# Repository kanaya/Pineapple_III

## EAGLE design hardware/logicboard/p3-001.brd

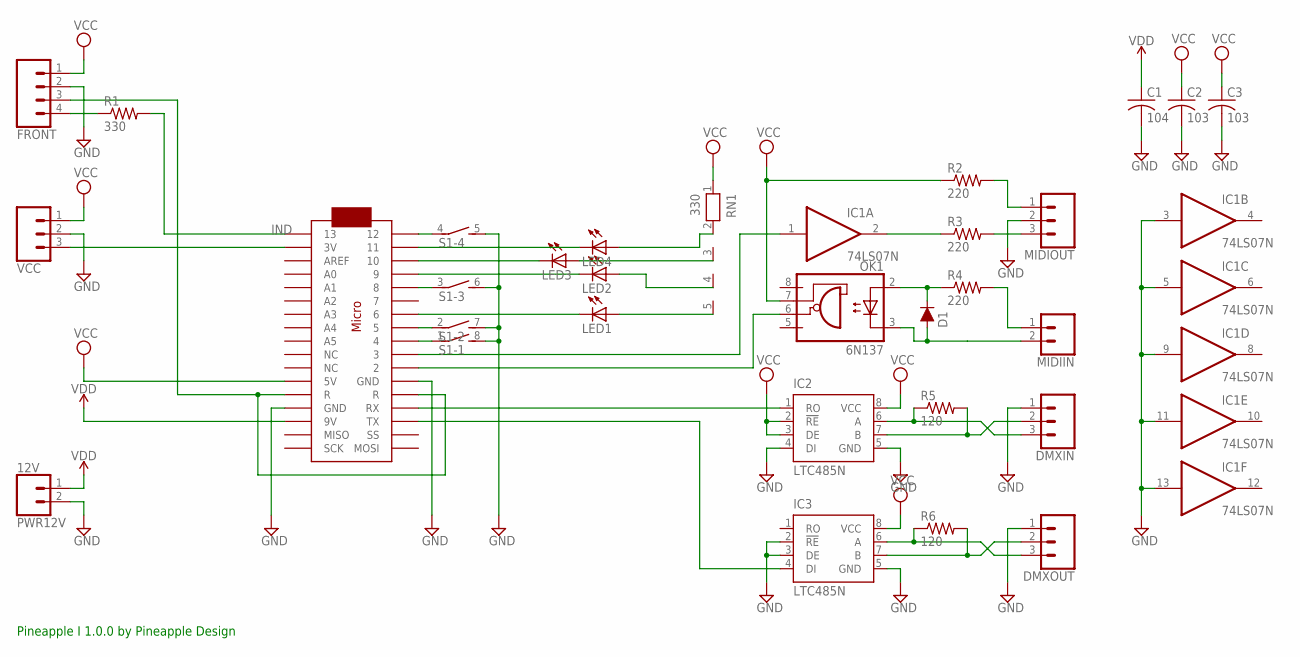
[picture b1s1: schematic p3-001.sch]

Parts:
C1: 104; C025-025X050
C2, C3: 103; C025-025X050
D1: DIODE-1N4148
DMXIN: CONN_03JST-PTH; JST-3-PTH
DMXOUT: CONN_03JST-PTH; JST-3-PTH
FRONT: CONN_04JST-PTH; JST-4-PTH
IC1: 74LS07N; DIL14
IC2, IC3: LTC485N; DIL08
LED1, LED2, LED3, LED4: LED3MM
MIDIIN: CONN_02JST-PTH-2; JST-2-PTH
MIDIOUT: CONN_03JST-PTH; JST-3-PTH
OK1: 6N137; DIL08
PWR12V: 12V; JST-2-PTH
R1: 330; 0204/5
R2, R3, R4: 220; 0204/5
R5, R6: 120; 0204/5
RN1: 330; RN-5
S1: DIP04S
U$1: ARDUINOMICRO
VCC: CONN_03JST-PTH; JST-3-PTH

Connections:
GND: C1.2, C2.2, C3.2, DMXIN.1, DMXOUT.1, FRONT.2, IC1.3 (I), IC1.5 (I), IC1.7 (GND), IC1.9 (I), IC1.11 (I), IC1.13 (I), IC2.4 (DI), IC2.5 (GND), IC3.2 (!RE), IC3.3 (DE), IC3.5 (GND), MIDIOUT.2, PWR12V.2, S1.5 (2), S1.6 (2), S1.7 (2), S1.8 (2), U$1.P$12 (GND), U$1.P$21 (GND), VCC.2
IND: R1.2, U$1.P$34 (13)
MIDIIN+: MIDIIN.1, R4.2
MIDIIN-: D1.A, MIDIIN.2, OK1.3 (C)
MIDITHRU+: MIDIOUT.1, R2.2
MIDITHRU-: MIDIOUT.3, R3.2
unnamed: DMXIN.3, IC2.6 (A), R5.1
unnamed: IC1.2 (O), R3.1
unnamed: FRONT.4, R1.1
unnamed: DMXIN.2, IC2.7 (B), R5.2
unnamed: D1.C, OK1.2 (A), R4.1
unnamed: IC1.1 (I), U$1.P$10 (3)
unnamed: IC3.4 (DI), U$1.P$15 (TX)
unnamed: DMXOUT.3, IC3.6 (A), R6.1
unnamed: DMXOUT.2, IC3.7 (B), R6.2
unnamed: IC2.1 (RO), U$1.P$14 (RX)
unnamed: LED1.K (C), U$1.P$7 (6)
unnamed: LED2.K (C), U$1.P$4 (9)
unnamed: LED3.K (C), U$1.P$3 (10)
unnamed: LED4.K (C), U$1.P$2 (11)
unnamed: LED1.A, RN1.5
unnamed: LED2.A, RN1.4
unnamed: LED3.A, RN1.3
unnamed: LED4.A, RN1.2
unnamed: S1.1, U$1.P$9 (4)
unnamed: S1.2 (1), U$1.P$8 (5)
unnamed: S1.3 (1), U$1.P$5 (8)
unnamed: S1.4 (1), U$1.P$1 (12)
RST: FRONT.3, U$1.P$13 (R), U$1.P$22 (R)
RX: OK1.6 (VO), U$1.P$11 (2)
V3V: U$1.P$33 (3V), VCC.3
VCC: C2.1, C3.1, FRONT.1, IC1.14 (VCC), IC2.2 (!RE), IC2.3 (DE), IC2.8 (VCC), IC3.8 (VCC), OK1.7 (VE), R2.1, RN1.1, U$1.P$23 (5V), VCC.1
VDD: C1.1, PWR12V.1, U$1.P$20 (9V)

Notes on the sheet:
Pineapple I 1.0.0 by Pineapple Design

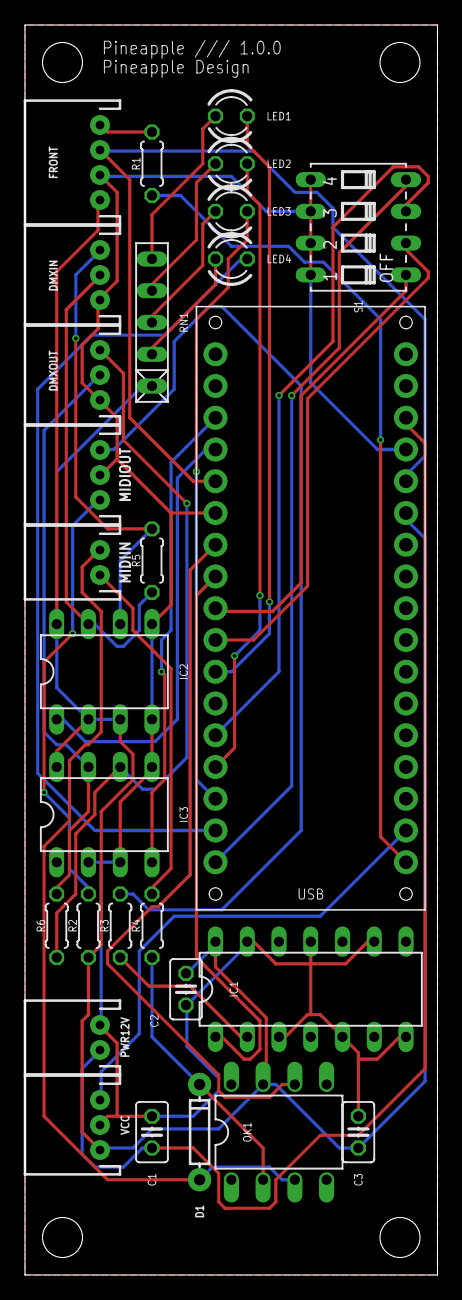
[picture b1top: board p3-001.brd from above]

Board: 2 copper layers, 33.0 x 100.0 mm, 28 parts (0 on the bottom side), 33 nets.

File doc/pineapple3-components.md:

# Pineapple III Components

## 半導体

* Arduino Micro 5V ピンヘッダ無し, x1
* 74LS07N, x1
* TLP552, x1
* LTC485N, x1
* 小信号用ダイオード, x1

## 受動素子

* 集積抵抗
** 4素子330, x1
* 抵抗
** 120, x2
** 220, x3
** 330, x1
* キャパシタ
** 0.01u, x2
** 0.1u, x1

## 機構

* スイッチ
** 照明内蔵モーメンタリプッシュスイッチ（緑）, x1
** 4-bit DIP スイッチ, x1
* コネクタ
** パネルマウントDCジャック, x1
** パネルマウント DIN 5p レセプタクル, x1
** パネルマウント DIN 8p レセプタクル, x1
** パネルマウント XLR 3p レセプタクル雄, x1
** パネルマウント XLR 3p レセプタクル雌, x1
** USB Mini B プラグ, x1
** 2p PH コネクタ, x2
** 3p PH コネクタ, x2
** 4p PH コネクタ, x1
** 2p PH ハーネス, x2
** 3p PH ハーネス, x2
** 4p PH ハーネス, x1

## 基板とケース

* Pineapple III 基板 (42mm x 83mm)
* タカチ MX4-10-15
* タカチ EXP12-6-9/13/18

## 電源

* DC12V1A電源

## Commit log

2018-07-25 New .gitignore.
2018-07-29 Initial design.
2018-07-29 DIP SW.
2018-07-29 100mm board.
2018-07-29 Doc.
2018-08-03 Clean up.
2018-08-03 .gitignore.
2018-08-10 Document update.

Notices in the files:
parts and their libraries:
SparkFun-DiscreteSemi: Licensing: Creative Commons ShareAlike 4.0 International - https://creativecommons.org/licenses/by-sa/4.0
